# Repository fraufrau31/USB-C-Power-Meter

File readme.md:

# The USB-C Power Meter
This project is an open-source power meter over USB-C and compliant with USB Power Delivery 3.0.

## Current Status
- Still under development.

## Hardware
- Acquisition is made trough INA700 with an integrated shunt.
- Acquisition board use a SSD1306-based I2C OLED Module to display data.

## Software
- Still under development.

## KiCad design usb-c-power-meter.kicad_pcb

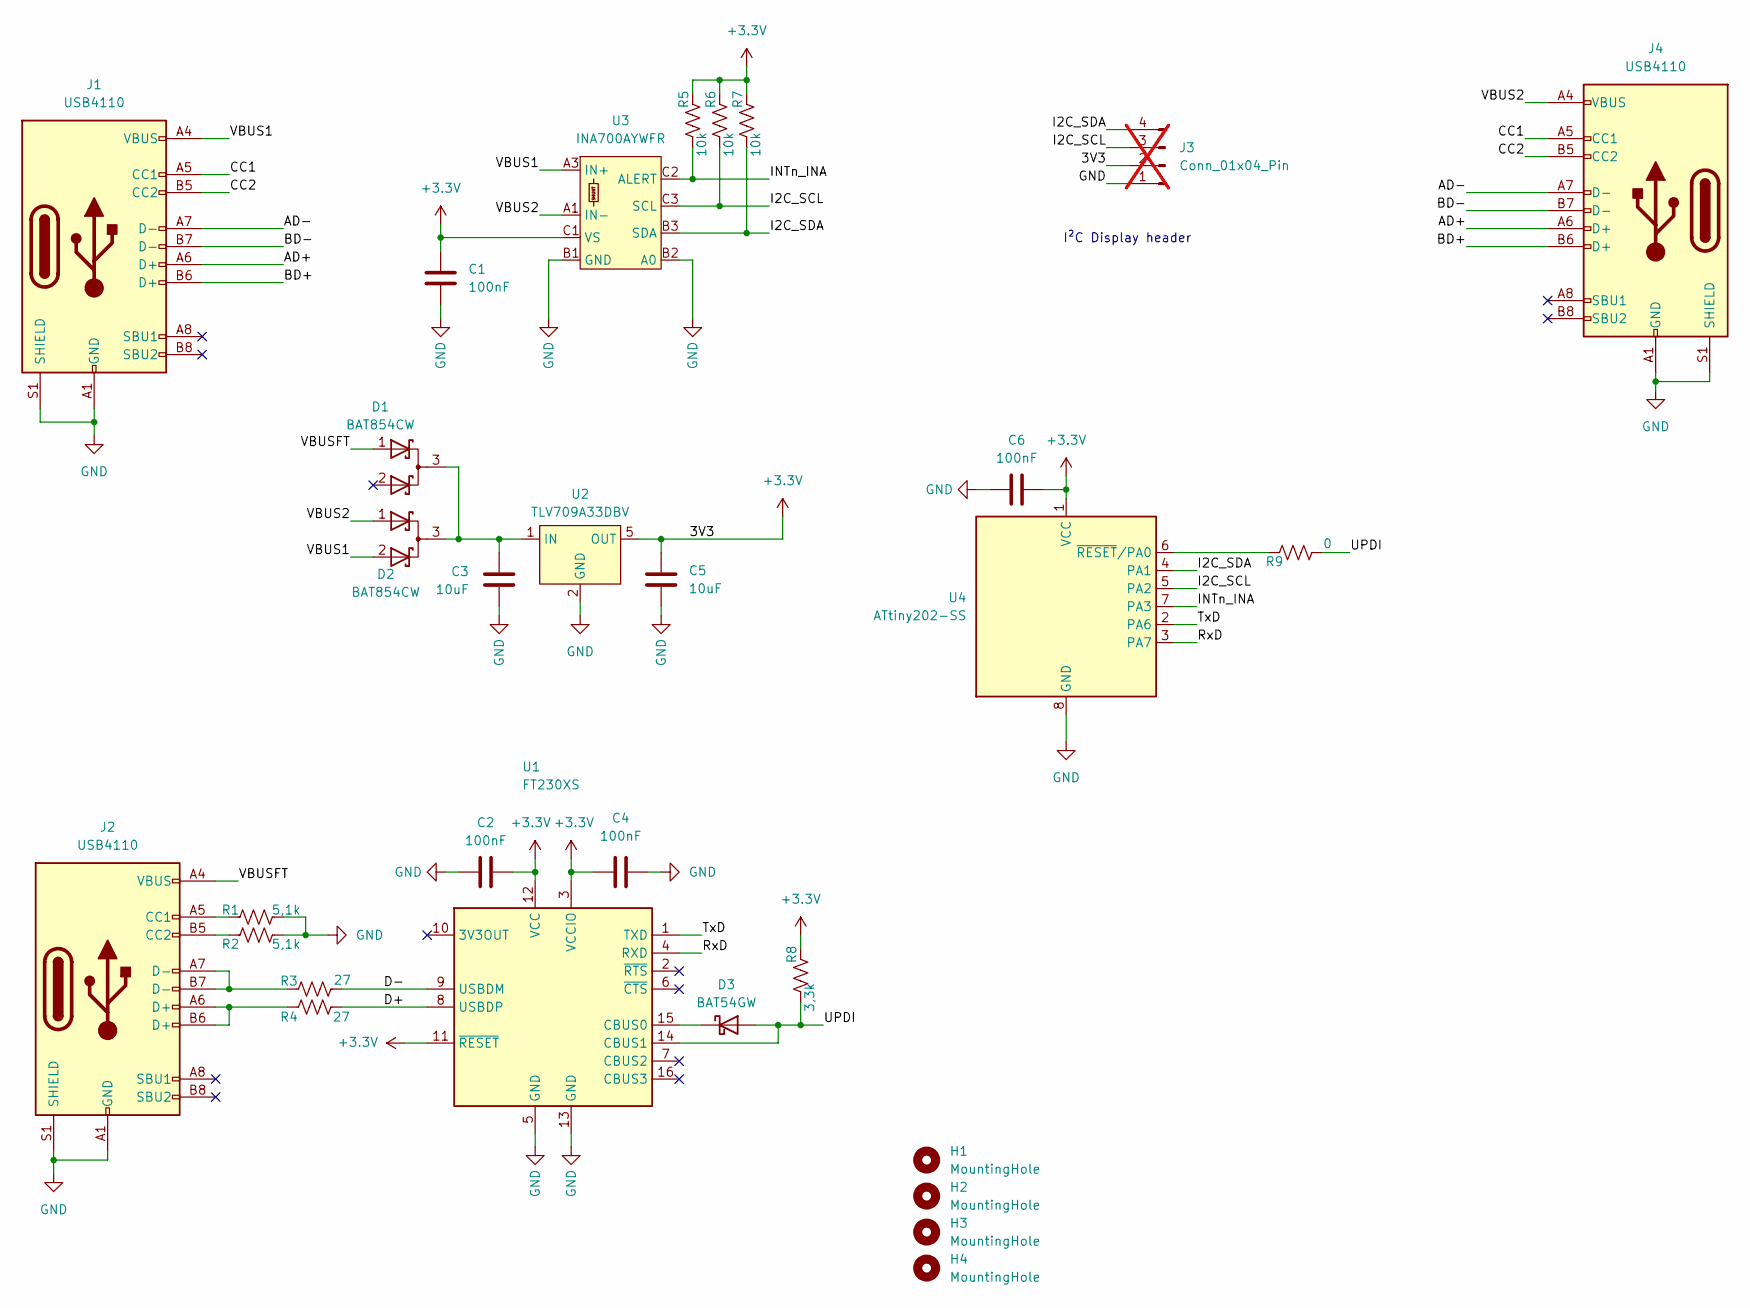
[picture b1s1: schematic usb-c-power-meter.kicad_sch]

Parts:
C1, C2, C4, C6: 100nF; C_0603_1608Metric; DIGIKEY 311-1088-1-ND
C3: 10uF; C_1206_3216Metric; DIGIKEY 1276-2876-1-ND
C5: 10uF; C_0805_2012Metric; DIGIKEY 1276-1096-1-ND
D1, D2: BAT854CW; SOT-323_SC-70; DIGIKEY 1727-1211-1-ND
D3: BAT54GW; D_SOD-123; DIGIKEY 1727-7328-1-ND
H1, H2, H3, H4: MountingHole; MountingHole_2.2mm_M2
J1, J2, J4: USB4110; USB_C_Receptacle_GCT_USB4110; DIGIKEY 2073-USB4110-GF-A-1-ND
J3: Conn_01x04_Pin; PinHeader_1x04_P2.54mm_Vertical; not fitted
R1, R2: 5,1k; R_0603_1608Metric; DIGIKEY 311-5.10KHRCT-ND
R3, R4: 27; R_0603_1608Metric; DIGIKEY 311-27.0HRCT-ND
R5, R6, R7: 10k; R_0603_1608Metric; DIGIKEY 311-10.0KHRCT-ND
R8: 3,3k; R_0603_1608Metric; DIGIKEY 311-3.30KHRCT-ND
R9: 0; R_0603_1608Metric; DIGIKEY 311-0.0GRCT-ND
U1: FT230XS; SSOP-16_3.9x4.9mm_P0.635mm; DIGIKEY 768-1135-1-ND
U2: TLV709A33DBV; SOT-23-5; DIGIKEY 296-TLV709A33DBVRCT-ND
U3: INA700AYWFR; YWF0008A; DIGIKEY 296-INA700AYWFRCT-ND
U4: ATtiny202-SS; SOIC-8_3.9x4.9mm_P1.27mm; DIGIKEY ATTINY202-SSFRCT-ND

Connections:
+3.3V: C1.1, C2.2, C4.1, C5.1, C6.2, J3.2, R5.2, R6.2, R7.2, R8.2, U1.3 (VCCIO), U1.11 (~RESET), U1.12 (VCC), U2.5 (OUT), U3.C1 (VS), U4.1 (VCC)
/AD+: J1.A6 (D+), J4.A6 (D+)
/AD-: J1.A7 (D-), J4.A7 (D-)
/BD+: J1.B6 (D+), J4.B6 (D+)
/BD-: J1.B7 (D-), J4.B7 (D-)
/CC1: J1.A5 (CC1), J4.A5 (CC1)
/CC2: J1.B5 (CC2), J4.B5 (CC2)
/D+: R4.1, U1.8 (USBDP)
/D-: R3.1, U1.9 (USBDM)
/I2C_SCL: J3.3, R6.1, U3.C3 (SCL), U4.5 (PA2)
/I2C_SDA: J3.4, R7.1, U3.B3 (SDA), U4.4 (PA1)
/INTn_INA: R5.1, U3.C2 (ALERT), U4.7 (PA3)
/RxD: U1.4 (RXD), U4.3 (PA7)
/TxD: U1.1 (TXD), U4.2 (PA6)
/UPDI: D3.2 (A), R8.1, R9.1, U1.14 (CBUS1)
/VBUS1: D2.2 (K), J1.A4 (VBUS), J1.A9 (VBUS), J1.B4 (VBUS), J1.B9 (VBUS), U3.A3 (IN+)
/VBUS2: D2.1 (K), J4.A4 (VBUS), J4.A9 (VBUS), J4.B4 (VBUS), J4.B9 (VBUS), U3.A1 (IN-)
/VBUSFT: D1.1 (K), J2.A4 (VBUS), J2.A9 (VBUS), J2.B4 (VBUS), J2.B9 (VBUS)
GND: C1.2, C2.1, C3.2, C4.2, C5.2, C6.1, J1.A1 (GND), J1.A12 (GND), J1.B1 (GND), J1.B12 (GND), J1.S1 (SHIELD), J2.A1 (GND), J2.A12 (GND), J2.B1 (GND), J2.B12 (GND), J2.S1 (SHIELD), J3.1, J4.A1 (GND), J4.A12 (GND), J4.B1 (GND), J4.B12 (GND), J4.S1 (SHIELD), R1.1, R2.1, U1.5 (GND), U1.13 (GND), U2.2 (GND), U3.B1 (GND), U3.B2 (A0), U4.8 (GND)
unnamed: C3.1, D1.3 (A), D2.3 (A), U2.1 (IN)
unnamed: D3.1 (K), U1.15 (CBUS0)
unnamed: J2.A5 (CC1), R1.2
unnamed: J2.B5 (CC2), R2.2
unnamed: J2.A6 (D+), J2.B6 (D+), R4.2
unnamed: J2.A7 (D-), J2.B7 (D-), R3.2
unnamed: R9.2, U4.6 (~RESET/PA0)

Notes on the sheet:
I²C Display header

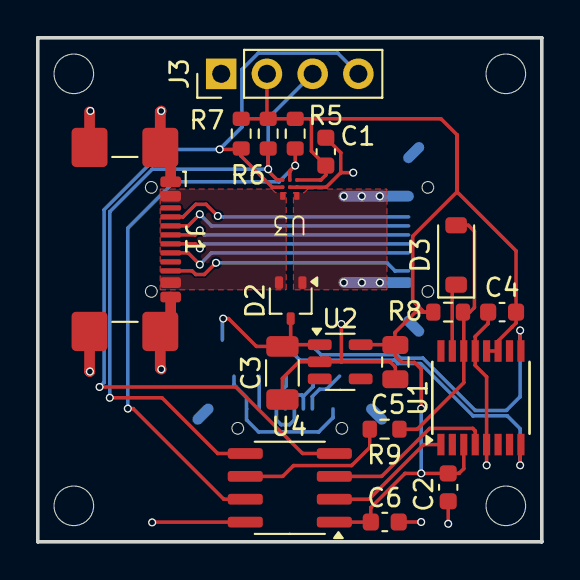
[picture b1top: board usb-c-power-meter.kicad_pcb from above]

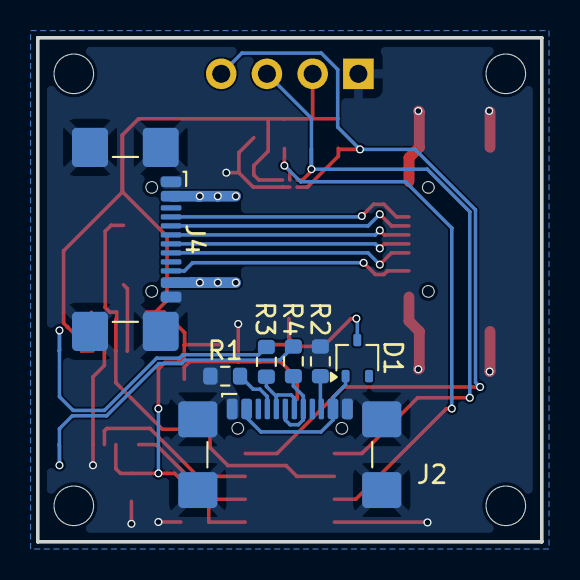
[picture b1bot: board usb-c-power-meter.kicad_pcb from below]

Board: 2 copper layers, 28.0 x 28.0 mm, 30 parts (7 on the bottom side), 26 nets.

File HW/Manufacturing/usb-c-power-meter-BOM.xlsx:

Reference | Value | Description | Footprint | Qty | DNP | Mfr. No | DIGIKEY | FARNELL | MOUSER
C1,C2,C4,C6 | 100nF | C Ceramic, 100nF, 16V, ±10%, 0603 | Capacitor_SMD:C_0603_1608Metric | 4 |  | CC0603KRX7R7BB104 | 311-1088-1-ND | 2408501 | 603-CC603KRX7R7BB104
C3 | 10uF | C Ceramic, 10uF, 50V, ±10%, 1206 | Capacitor_SMD:C_1206_3216Metric | 1 |  | CL31A106KBHNNNE | 1276-2876-1-ND | 3013512 | 187-CL31A106KBHNNNE
C5 | 10uF | C Ceramic, 10uF, 16V, ±10%, 0805 | Capacitor_SMD:C_0805_2012Metric | 1 |  | CL21A106KOQNNNE | 1276-1096-1-ND | 3013453 | 187-CL21A106KOQNNNE
D1,D2 | BAT854CW | Dual Schottky diode, common anode on pin 1 | Package_TO_SOT_SMD:SOT-323_SC-70 | 2 |  | BAT854CW | 1727-1211-1-ND | 3912169 | 771-BAT854CW,135
D3 | BAT54GW | 30 V, 200 mA Schottky barrier diodes | Diode_SMD:D_SOD-123 | 1 |  | BAT54GWJ | 1727-7328-1-ND | 3439596 | 841-BAT54GWJ
J1,J2,J4 | USB4110 | Type C USB 2.0 Connector | Connector_USB:USB_C_Receptacle_GCT_USB4110 | 3 |  | USB4110-GF-A | 2073-USB4110-GF-A-1-ND | 3588206 | 640-USB4110-GF-A
J3 | Conn_01x04_Pin | Generic connector, single row, 01x04, script generated | Connector_PinHeader_2.54mm:PinHeader_1x04_P2.54mm_Vertical | 1 | DNP
R1,R2 | 5,1k | R, 5,1kOhms, ±1%, 0.1W, 1/10W, 0603 | Resistor_SMD:R_0603_1608Metric | 2 |  | RC0603FR-075K1L | 311-5.10KHRCT-ND | 3495881 | 603-RC0603FR-075K1L
R3,R4 | 27 | R, 27Ohms, ±1%, 0.1W, 1/10W, 0603 | Resistor_SMD:R_0603_1608Metric | 2 |  | RC0603FR-0727RL | 311-27.0HRCT-ND | 9238298 | 603-RC0603FR-0727RL
R5,R6,R7 | 10k | R, 10kOhms, ±1%, 0.1W, 1/10W, 0603 | Resistor_SMD:R_0603_1608Metric | 3 |  | RC0603FR-0710KL | 311-10.0KHRCT-ND | 9238603 | 603-RC0603FR-0710KL
R8 | 3,3k | R, 3,3kOhms, ±1%, 0.1W, 1/10W, 0603 | Resistor_SMD:R_0603_1608Metric | 1 |  | RC0603FR-073K3L | 311-3.30KHRCT-ND | 9238549 | 603-RC0603FR-073K3L
R9 | 0 | R, 0Ohms, ±1%, 0.1W, 1/10W, 0603 | Resistor_SMD:R_0603_1608Metric | 1 |  | RC0603JR-070RL | 311-0.0GRCT-ND | 9233130 | 603-RC0603JR-070RL
U1 | FT230XS | Full Speed USB to Basic UART, SSOP-16 | Package_SO:SSOP-16_3.9x4.9mm_P0.635mm | 1 |  | FT230XS-R | 768-1135-1-ND | 2081321 | 895-FT230XS-R
U2 | TLV709A33DBV | TLV709 150mA, 30V, 3.2μA Quiescent Current, Low-Dropout Linear Regulator | Package_TO_SOT_SMD:SOT-23-5 | 1 |  | TLV709A33DBV | 296-TLV709A33DBVRCT-ND | # | 595-TLV709A33DBVR
U3 | INA700AYWFR | 40-V 16-Bit I²C output digital power monitor in WCSP with EZShunt™ Technology | usb-c-power-meter:YWF0008A | 1 |  | INA700AYWFR | 296-INA700AYWFRCT-ND | # | 595-INA700AYWFR
U4 | ATtiny202-SS | 20MHz, 2kB Flash, 128B SRAM, 64B EEPROM, SOIC-8 | Package_SO:SOIC-8_3.9x4.9mm_P1.27mm | 1 |  | ATTINY202-SSFR | ATTINY202-SSFRCT-ND | 3630362 | 579-ATTINY202-SSFR

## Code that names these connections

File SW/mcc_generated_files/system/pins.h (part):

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
/**
 * @ingroup  pinsdriver
 * @brief Default Interrupt Handler for IO_PA7 pin. 
 *        This is a predefined interrupt handler to be used together with the IO_PA7_SetInterruptHandler() method.
 *        This handler is called every time the IO_PA7 ISR is executed. 
 * @pre PIN_MANAGER_Initialize() has been called at least once
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
/**
 * @ingroup  pinsdriver
 * @brief Interrupt Handler Setter for IO_PA7 pin input-sense-config functionality.
 *        Allows selecting an interrupt handler for IO_PA7 at application runtime
 * @pre PIN_MANAGER_Initialize() has been called at least once
 * @param InterruptHandler function pointer.
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
/**
 * @ingroup  pinsdriver
 * @brief Default Interrupt Handler for IO_PA6 pin. 
 *        This is a predefined interrupt handler to be used together with the IO_PA6_SetInterruptHandler() method.
 *        This handler is called every time the IO_PA6 ISR is executed. 
 * @pre PIN_MANAGER_Initialize() has been called at least once
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
/**
 * @ingroup  pinsdriver
 * @brief Interrupt Handler Setter for IO_PA6 pin input-sense-config functionality.
 *        Allows selecting an interrupt handler for IO_PA6 at application runtime
 * @pre PIN_MANAGER_Initialize() has been called at least once
 * @param InterruptHandler function pointer.
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
/**
 * @ingroup  pinsdriver
 * @brief Default Interrupt Handler for IO_PA2 pin. 
 *        This is a predefined interrupt handler to be used together with the IO_PA2_SetInterruptHandler() method.
 *        This handler is called every time the IO_PA2 ISR is executed. 
 * @pre PIN_MANAGER_Initialize() has been called at least once
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
/**
 * @ingroup  pinsdriver
 * @brief Interrupt Handler Setter for IO_PA2 pin input-sense-config functionality.
 *        Allows selecting an interrupt handler for IO_PA2 at application runtime
 * @pre PIN_MANAGER_Initialize() has been called at least once
 * @param InterruptHandler function pointer.
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
/**
 * @ingroup  pinsdriver
 * @brief Default Interrupt Handler for IO_PA1 pin. 
 *        This is a predefined interrupt handler to be used together with the IO_PA1_SetInterruptHandler() method.
 *        This handler is called every time the IO_PA1 ISR is executed. 
 * @pre PIN_MANAGER_Initialize() has been called at least once
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
/**
 * @ingroup  pinsdriver
 * @brief Interrupt Handler Setter for IO_PA1 pin input-sense-config functionality.
 *        Allows selecting an interrupt handler for IO_PA1 at application runtime
 * @pre PIN_MANAGER_Initialize() has been called at least once
 * @param InterruptHandler function pointer.
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
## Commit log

2024-12-28 KiCAD project added
2025-01-03 Repo organisation update
2025-01-03 MPLAB X project added

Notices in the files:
SW/mcc_generated_files/system/pins.h:
© [2025] Microchip Technology Inc. and its subsidiaries.
